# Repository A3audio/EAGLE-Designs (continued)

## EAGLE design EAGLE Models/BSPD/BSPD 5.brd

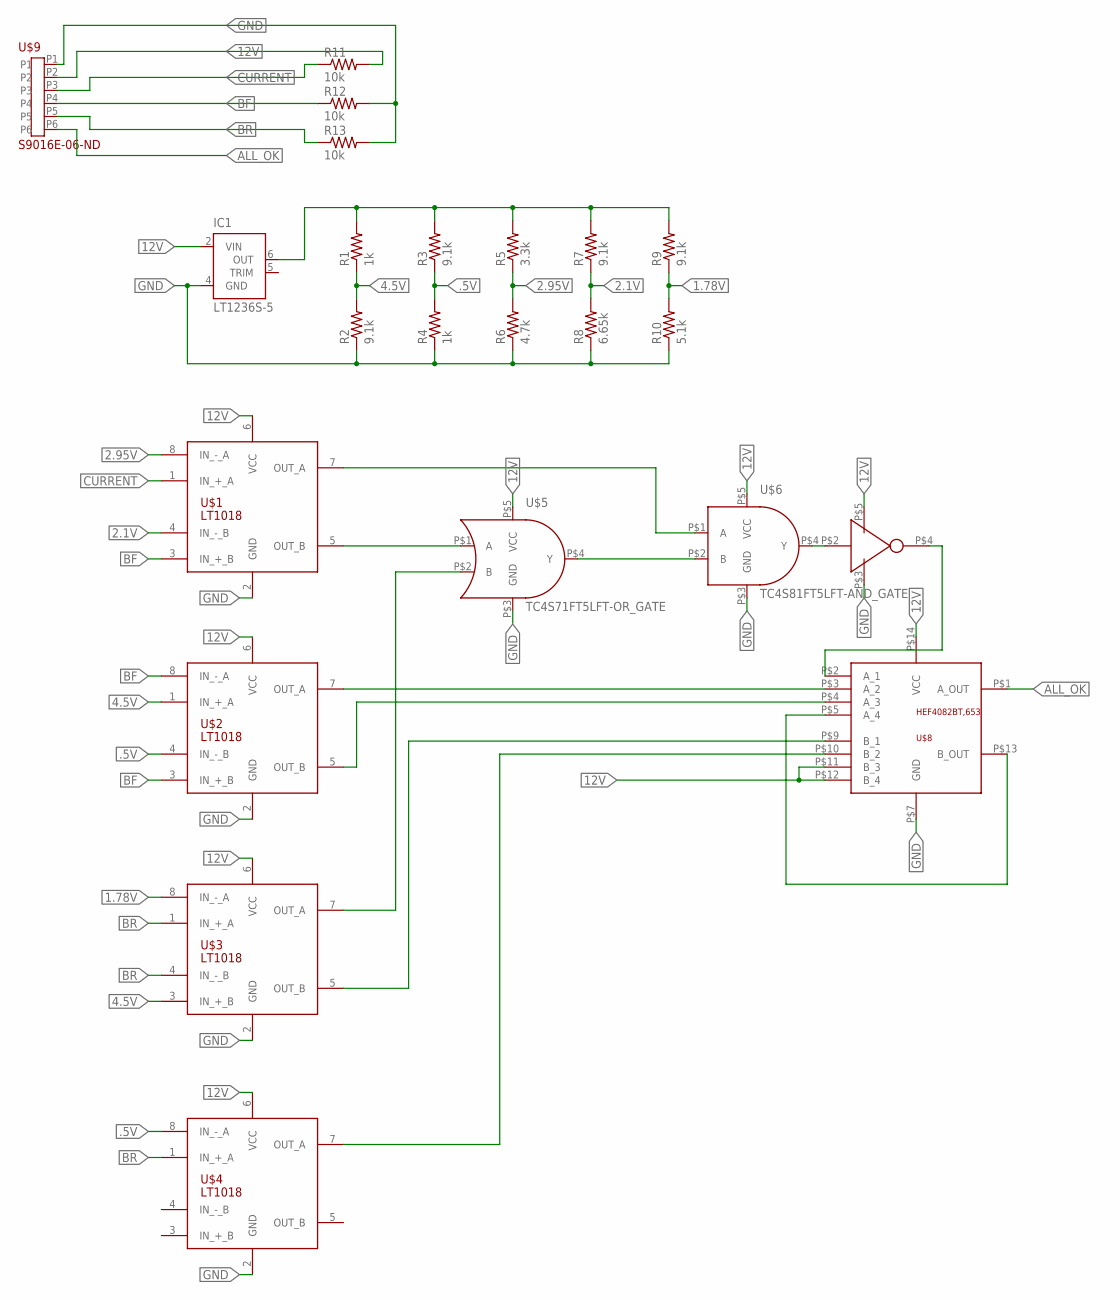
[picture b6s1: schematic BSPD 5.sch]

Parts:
IC1: LT1236S-5; SOIC8
R1, R4: 1k; 0603-RES
R2, R3, R7, R9: 9.1k; 0603-RES
R5: 3.3k; 0603-RES
R6: 4.7k; 0603-RES
R8: 6.65k; 0603-RES
R10: 5.1k; 0603-RES
R11, R12, R13: 10k; 0603-RES
U$1, U$2, U$3, U$4: LT1018; SOIC8
U$5: TC4S71FT5LFT-OR_GATE; SSOP5-P-0.95
U$6: TC4S81FT5LFT-AND_GATE; SSOP5-P-0.95
U$7: TC4S69F(TE85L,F); SSOP5-P-0.95
U$8: HEF4082BT,653; NXP_14_SOIC
U$9: S9016E-06-ND; S9016E-05-ND

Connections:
1.78V: R9.1, R10.2, U$3.8 (IN_-_A)
2.1V: R7.1, R8.2, U$1.4 (IN_-_B)
2.95V: R5.1, R6.2, U$1.8 (IN_-_A)
4.5V: R1.1, R2.2, U$2.1 (IN_+_A), U$3.3 (IN_+_B)
12V: IC1.2 (VIN), R11.2, U$1.6 (VCC), U$2.6 (VCC), U$3.6 (VCC), U$4.6 (VCC), U$5.P$5 (VCC), U$6.P$5 (VCC), U$7.P$5 (VCC), U$8.P$11 (B_3), U$8.P$12 (B_4), U$8.P$14 (VCC), U$9.P2
.5V: R3.1, R4.2, U$2.4 (IN_-_B), U$4.8 (IN_-_A)
ALL_OK: U$8.P$1 (A_OUT), U$9.P6
BF: R12.1, U$1.3 (IN_+_B), U$2.3 (IN_+_B), U$2.8 (IN_-_A), U$9.P4
BR: R13.1, U$3.1 (IN_+_A), U$3.4 (IN_-_B), U$4.1 (IN_+_A), U$9.P5
CURRENT: R11.1, U$1.1 (IN_+_A), U$9.P3
GND: IC1.4 (GND), R2.1, R4.1, R6.1, R8.1, R10.1, R12.2, R13.2, U$1.2 (GND), U$2.2 (GND), U$3.2 (GND), U$4.2 (GND), U$5.P$3 (GND), U$6.P$3 (GND), U$7.P$3 (GND), U$8.P$7 (GND), U$9.P1
unnamed: IC1.6 (OUT), R1.2, R3.2, R5.2, R7.2, R9.2
unnamed: U$1.5 (OUT_B), U$5.P$1 (A)
unnamed: U$3.7 (OUT_A), U$5.P$2 (B)
unnamed: U$5.P$4 (Y), U$6.P$2 (B)
unnamed: U$1.7 (OUT_A), U$6.P$1 (A)
unnamed: U$6.P$4 (Y), U$7.P$2 (IN)
unnamed: U$7.P$4 (OUT), U$8.P$2 (A_1)
unnamed: U$2.7 (OUT_A), U$8.P$3 (A_2)
unnamed: U$2.5 (OUT_B), U$8.P$4 (A_3)
unnamed: U$8.P$5 (A_4), U$8.P$13 (B_OUT)
unnamed: U$3.5 (OUT_B), U$8.P$9 (B_1)
unnamed: U$4.7 (OUT_A), U$8.P$10 (B_2)

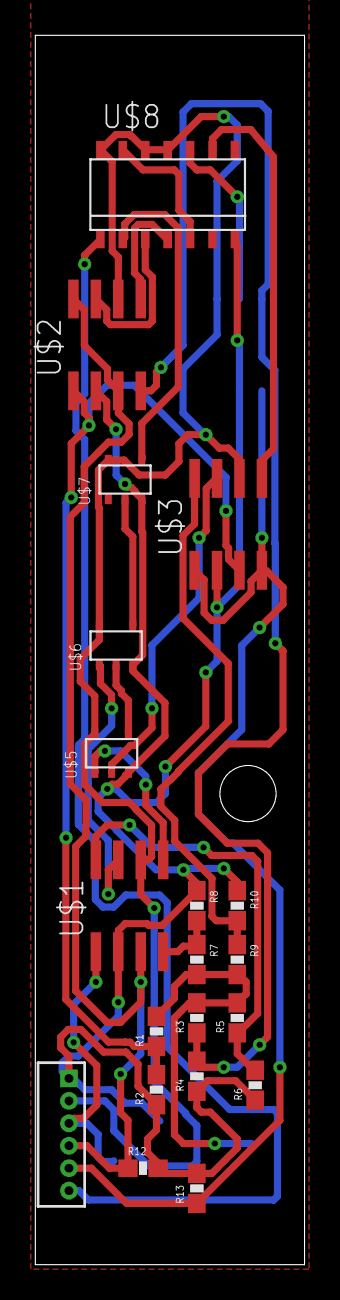
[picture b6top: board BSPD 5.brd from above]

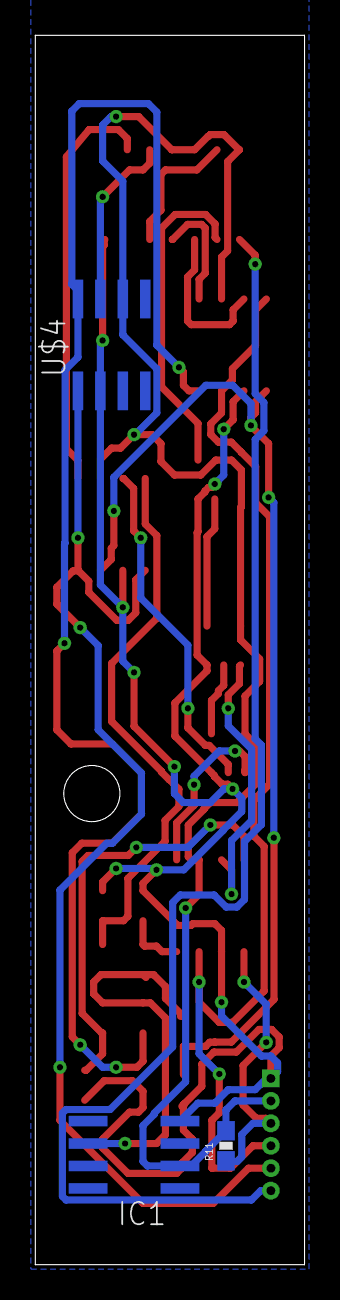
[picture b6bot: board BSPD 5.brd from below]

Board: 2 copper layers, 15.2 x 69.6 mm, 23 parts (3 on the bottom side), 23 nets.

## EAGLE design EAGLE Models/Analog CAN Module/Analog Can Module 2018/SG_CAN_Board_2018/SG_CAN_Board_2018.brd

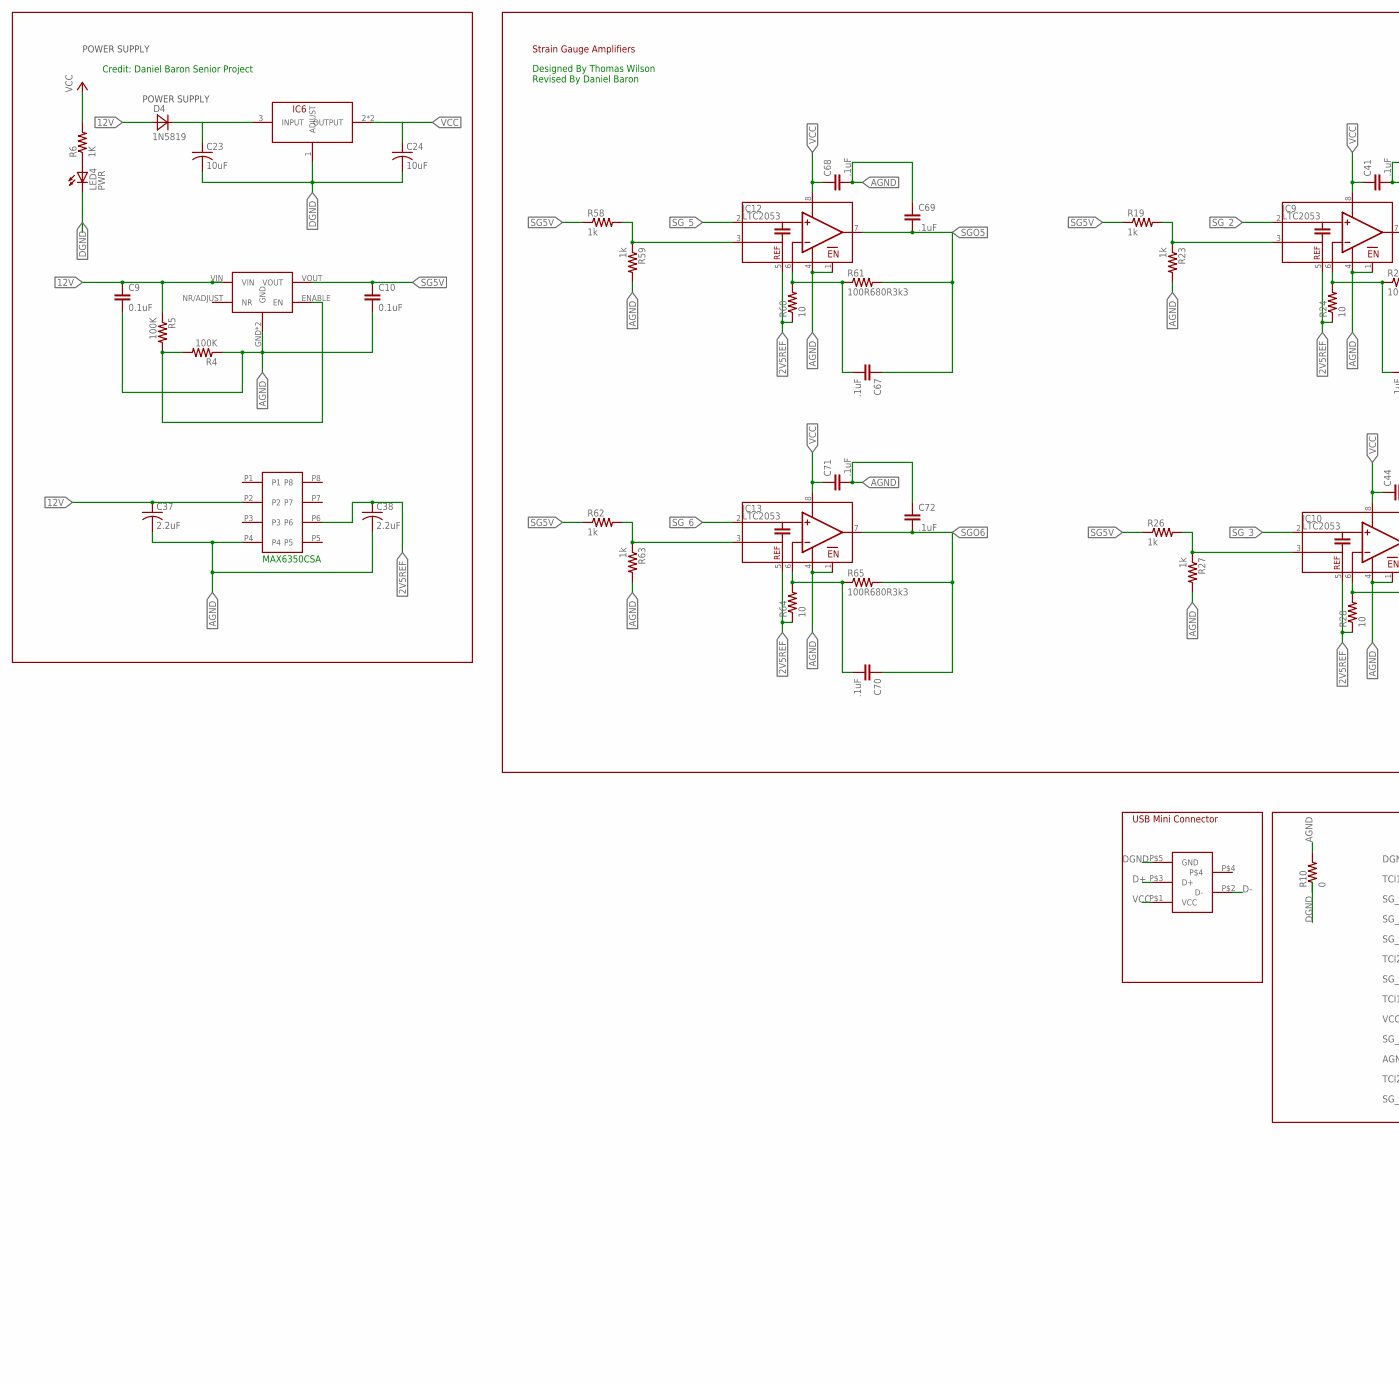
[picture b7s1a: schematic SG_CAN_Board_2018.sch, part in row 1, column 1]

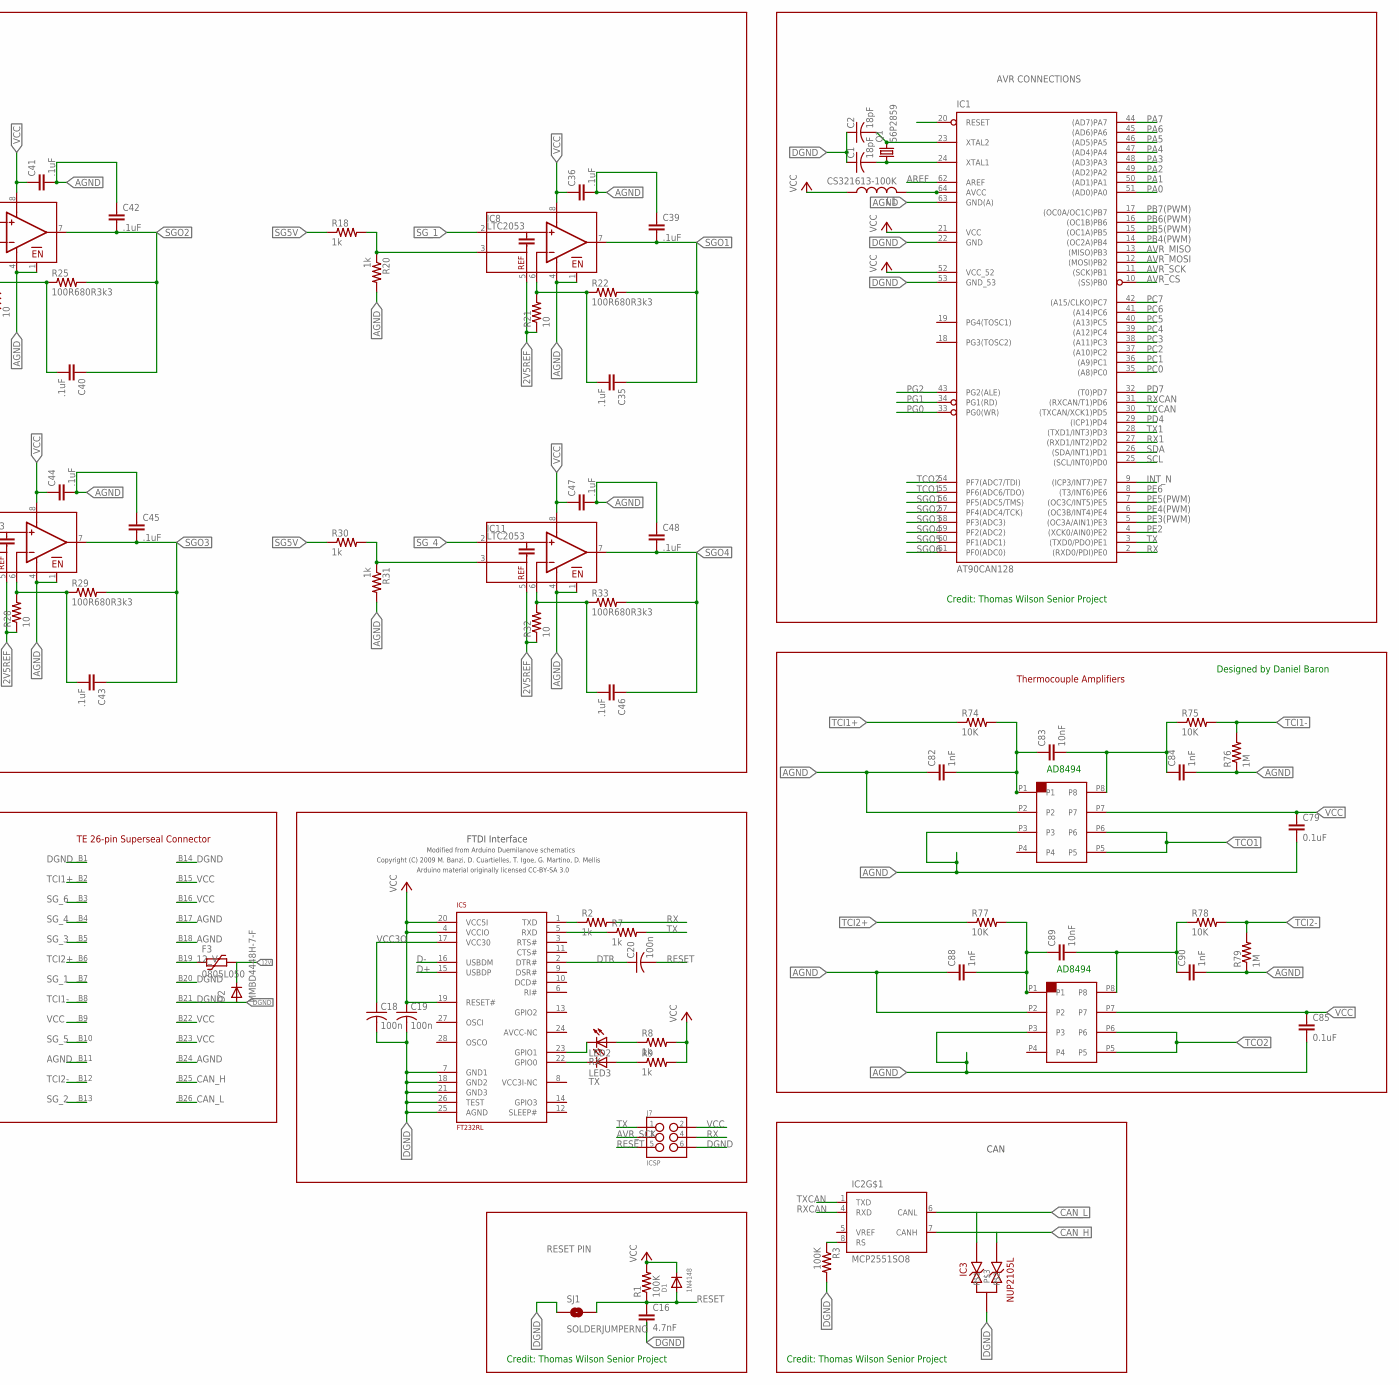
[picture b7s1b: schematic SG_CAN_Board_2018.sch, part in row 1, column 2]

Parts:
C1, C2: 18pF; C0805
C9, C10, C79, C85: 0.1uF; C0603
C16: 4.7nF; 0603-CAP
C18, C19, C20: 100n; C0805
C23, C24: 10uF; C0603
C35, C36, C39, C40, C41, C42, C43, C44, C45, C46, C47, C48, C67, C68, C69, C70, C71, C72: .1uF; 0603-CAP
C37, C38: 2.2uF; C0603
C82, C84, C88, C90: 1nF; C0603
C83, C89: 10nF; C0603
D1: 1N4148; SOD-123
D2: MMBD4448H-7-F; SOT23-3
D4: 1N5819; 1N5819SM
F3: 0805L050; 0805L
IC1: AT90CAN128; TQFP64
IC2: MCP2551SO8; SO08
IC3: NUP2105L; SOT-23
IC4: MAX6350CSA; 8-SOIC
IC5: FT232RL; SSOP28
IC6: NCP1117; SOT-223-4
IC7: REG-104GA-5; REG104GA-5
IC8, IC9, IC10, IC11, IC12, IC13: LTC2053; MSOP8
IC15, IC16: AD8495; 8MSOP
J1: 1734753-1_MINIUSB_CON
J2: SUPERSEAL1.0_26POS
J7: ICSP; 2X3_SMD_FCI_54202-G30
L1: CS321613-100K; L3216C
LED2: RX; CHIPLED_0805
LED3: TX; CHIPLED_0805
LED4: PWR; CHIPLED_0805
Q1: 56P2859; HC49UP
R1, R3: 100K; R0805
R2, R7, R8, R9: 1k; R0805
R4, R5: 100K; M0805
R6: 1K; R0805
R10: 0; 0603-RES
R18, R19, R20, R23, R26, R27, R30, R31, R58, R59, R62, R63: 1k; 0603-RES
R21, R24, R28, R32, R60, R64: 10; 0603-RES
R22, R25, R29, R33, R61, R65: 100R680R3k3; 0603-RES
R74, R75, R77, R78: 10K; 0603-RES
R76, R79: 1M; 0603-RES
SJ1: SOLDERJUMPERNO; SJ_2S-NO

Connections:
2V5REF: C38.1, IC4.P6, IC8.5 (REF), IC9.5 (REF), IC10.5 (REF), IC11.5 (REF), IC12.5 (REF), IC13.5 (REF), R21.1, R24.1, R28.1, R32.1, R60.1, R64.1
5V_REG_IN: C23.1, D4.P$2 (C), IC6.3 (INPUT)
12V: C9.1, C37.1, D2.3 (C), D4.P$1 (A), F3.1, IC4.P2, IC7.VIN, R5.1
12_V: F3.2, J2.B19
AGND: C9.2, C10.2, C36.2, C37.2, C38.2, C39.1, C41.2, C42.1, C44.2, C45.1, C47.2, C48.1, C68.2, C69.1, C71.2, C72.1, C79.2, C82.1, C84.2, C85.2, C88.1, C90.2, IC1.63 (GND(A)), IC4.P4, IC7.GND, IC7.HEATGND (GND), IC8.1 (EN), IC8.4 (V-), IC9.1 (EN), IC9.4 (V-), IC10.1 (EN), IC10.4 (V-), IC11.1 (EN), IC11.4 (V-), IC12.1 (EN), IC12.4 (V-), IC13.1 (EN), IC13.4 (V-), IC15.P2, IC15.P3, IC16.P2, IC16.P3, J2.B11, J2.B17, J2.B18, J2.B24, R4.1, R10.2, R20.2, R23.2, R27.2, R31.2, R59.2, R63.2, R76.1, R79.1
AREF: IC1.62 (AREF)
AVR_CS: IC1.10 ((SS)PB0)
AVR_MISO: IC1.13 ((MISO)PB3)
AVR_MOSI: IC1.12 ((MOSI)PB2)
AVR_SCK: IC1.11 ((SCK)PB1), J7.3
CAN_H: IC2.7 (CANH), IC3.2, J2.B25
CAN_L: IC2.6 (CANL), IC3.1, J2.B26
D+: IC5.15 (USBDP), J1.P$3 (D+)
D-: IC5.16 (USBDM), J1.P$2 (D-)
DGND: C1.1, C2.1, C18.2, C19.2, C23.2, C24.2, D2.1 (A), IC1.22 (GND), IC1.53 (GND_53), IC2.2 (GND), IC3.3, IC5.7 (GND1), IC5.18 (GND2), IC5.21 (GND3), IC5.25 (AGND), IC5.26 (TEST), IC6.1 (ADJUST), J1.P$5 (GND), J2.B1, J2.B14, J2.B20, J2.B21, J7.6, LED4.C, R3.2, R10.1, SJ1.1
DTR: C20.1, IC5.2 (DTR#)
INT_N: IC1.9 ((ICP3/INT7)PE7)
M8RXD: IC5.1 (TXD), R2.1
M8TXD: IC5.5 (RXD), R7.1
unnamed: C35.2, IC8.6 (RG), R21.2, R22.1
unnamed: IC7.ENABLE (EN), R4.2, R5.2
unnamed: IC8.3 (+IN), R18.2, R20.1
unnamed: IC9.3 (+IN), R19.2, R23.1
unnamed: IC2.8 (RS), R3.1
unnamed: C40.2, IC9.6 (RG), R24.2, R25.1
unnamed: IC10.3 (+IN), R26.2, R27.1
unnamed: LED4.A, R6.1
unnamed: C43.2, IC10.6 (RG), R28.2, R29.1
unnamed: C1.2, IC1.24 (XTAL1), Q1.1
unnamed: IC11.3 (+IN), R30.2, R31.1
unnamed: C46.2, IC11.6 (RG), R32.2, R33.1
unnamed: IC1.64 (AVCC), L1.2
unnamed: IC12.3 (+IN), R58.2, R59.1
unnamed: C67.2, IC12.6 (RG), R60.2, R61.1
unnamed: IC13.3 (+IN), R62.2, R63.1
unnamed: C70.2, IC13.6 (RG), R64.2, R65.1
unnamed: IC5.23 (GPIO1), LED2.C
unnamed: IC5.22 (GPIO0), LED3.C
unnamed: LED2.A, R8.1
unnamed: LED3.A, R9.1
unnamed: C88.2, C89.1, IC16.P1, R77.2
unnamed: C83.2, C84.1, IC15.P8, R75.1
unnamed: C89.2, C90.1, IC16.P8, R78.1
unnamed: C82.2, C83.1, IC15.P1, R74.2
PA0: IC1.51 ((AD0)PA0)
PA1: IC1.50 ((AD1)PA1)
PA2: IC1.49 ((AD2)PA2)
PA3: IC1.48 ((AD3)PA3)
PA4: IC1.47 ((AD4)PA4)
PA5: IC1.46 ((AD5)PA5)
PA6: IC1.45 ((AD6)PA6)
PA7: IC1.44 ((AD7)PA7)
PB4(PWM): IC1.14 ((OC2A)PB4)
PB5(PWM): IC1.15 ((OC1A)PB5)
PB6(PWM): IC1.16 ((OC1B)PB6)
PB7(PWM): IC1.17 ((OC0A/OC1C)PB7)
PC0: IC1.35 ((A8)PC0)
PC1: IC1.36 ((A9)PC1)
PC2: IC1.37 ((A10)PC2)
PC3: IC1.38 ((A11)PC3)
PC4: IC1.39 ((A12)PC4)
PC5: IC1.40 ((A13)PC5)
PC6: IC1.41 ((A14)PC6)
PC7: IC1.42 ((A15/CLKO)PC7)
PD4: IC1.29 ((ICP1)PD4)
PD7: IC1.32 ((T0)PD7)
PE2: IC1.4 ((XCK0/AIN0)PE2)
PE3(PWM): IC1.5 ((OC3A/AIN1)PE3)
PE4(PWM): IC1.6 ((OC3B/INT4)PE4)
PE5(PWM): IC1.7 ((OC3C/INT5)PE5)
PE6: IC1.8 ((T3/INT6)PE6)
PG0: IC1.33 (PG0(WR))
PG1: IC1.34 (PG1(RD))
PG2: IC1.43 (PG2(ALE))
RESET: C16.1, C20.2, D1.A, IC1.20 (RESET), J7.5, R1.1, SJ1.2
RX: IC1.2 ((RXD0/PDI)PE0), J7.4, R2.2
RX1: IC1.27 ((RXD1/INT2)PD2)
RXCAN: IC1.31 ((RXCAN/T1)PD6), IC2.4 (RXD)
SCL: IC1.25 ((SCL/INT0)PD0)
SDA: IC1.26 ((SDA/INT1)PD1)
SG5V: C10.1, IC7.VOUT, R18.1, R19.1, R26.1, R30.1, R58.1, R62.1
SGO1: C35.1, C39.2, IC1.56 (PF5(ADC5/TMS)), IC8.7 (OUT), R22.2
SGO2: C40.1, C42.2, IC1.57 (PF4(ADC4/TCK)), IC9.7 (OUT), R25.2
SGO3: C43.1, C45.2, IC1.58 (PF3(ADC3)), IC10.7 (OUT), R29.2
SGO4: C46.1, C48.2, IC1.59 (PF2(ADC2)), IC11.7 (OUT), R33.2
SGO5: C67.1, C69.2, IC1.60 (PF1(ADC1)), IC12.7 (OUT), R61.2
SGO6: C70.1, C72.2, IC1.61 (PF0(ADC0)), IC13.7 (OUT), R65.2
SG_1: IC8.2 (-IN), J2.B7
SG_2: IC9.2 (-IN), J2.B13
SG_3: IC10.2 (-IN), J2.B5
SG_4: IC11.2 (-IN), J2.B4
SG_5: IC12.2 (-IN), J2.B10
SG_6: IC13.2 (-IN), J2.B3
TCI1+: J2.B2, R74.1
TCI1-: J2.B8, R75.2, R76.2
TCI2+: J2.B6, R77.1
TCI2-: J2.B12, R78.2, R79.2
TCO1: IC1.55 (PF6(ADC6/TDO)), IC15.P5, IC15.P6
TCO2: IC1.54 (PF7(ADC7/TDI)), IC16.P5, IC16.P6
TX: IC1.3 ((TXD0/PDO)PE1), J7.1, R7.2
TX1: IC1.28 ((TXD1/INT3)PD3)
TXCAN: IC1.30 ((TXCAN/XCK1)PD5), IC2.1 (TXD)
VCC: C19.1, C24.1, C36.1, C41.1, C44.1, C47.1, C68.1, C71.1, C79.1, C85.1, D1.C, IC1.21 (VCC), IC1.52 (VCC_52), IC2.3 (VCC), IC5.4 (VCCIO), IC5.19 (RESET#), IC5.20 (VCC5I), IC6.2 (OUTPUT), IC6.4 (OUTPUT), IC8.8 (V+), IC9.8 (V+), IC10.8 (V+), IC11.8 (V+), IC12.8 (V+), IC13.8 (V+), IC15.P7, IC16.P7, J1.P$1 (VCC), J2.B9, J2.B15, J2.B16, J2.B22, J2.B23, J7.2, L1.1, R1.2, R6.2, R8.2, R9.2
VCC3O: C18.1, IC5.17 (VCC30)
XTAL1: C2.2, IC1.23 (XTAL2), Q1.2

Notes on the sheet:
CAN
AVR CONNECTIONS
Thermocouple Amplifiers
Credit: Thomas Wilson Senior Project
Designed by Daniel Baron
AD8494
Strain Gauge Amplifiers
RESET PIN
FTDI Interface
Modified from Arduino Duemilanove schematics
Copyright (C) 2009 M. Banzi, D. Cuartielles, T. Igoe, G. Martino, D. Mellis
Arduino material originally licensed CC-BY-SA 3.0
Designed By Thomas Wilson Revised By Daniel Baron
USB Mini Connector
POWER SUPPLY
MAX6350CSA
Credit: Daniel Baron Senior Project
TE 26-pin Superseal Connector

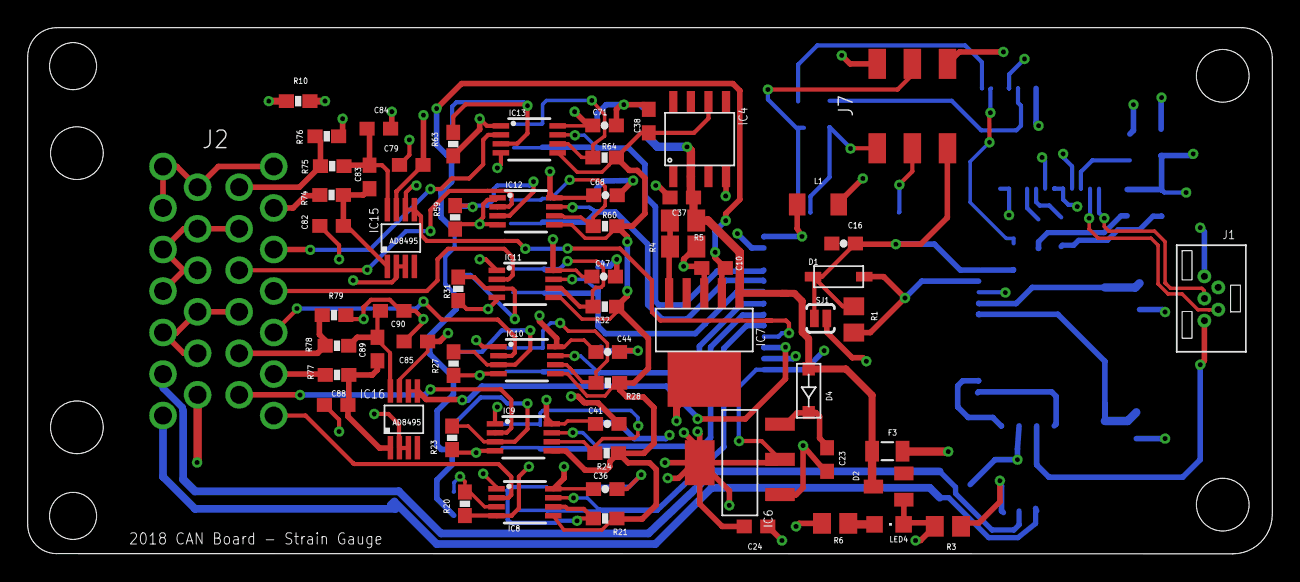
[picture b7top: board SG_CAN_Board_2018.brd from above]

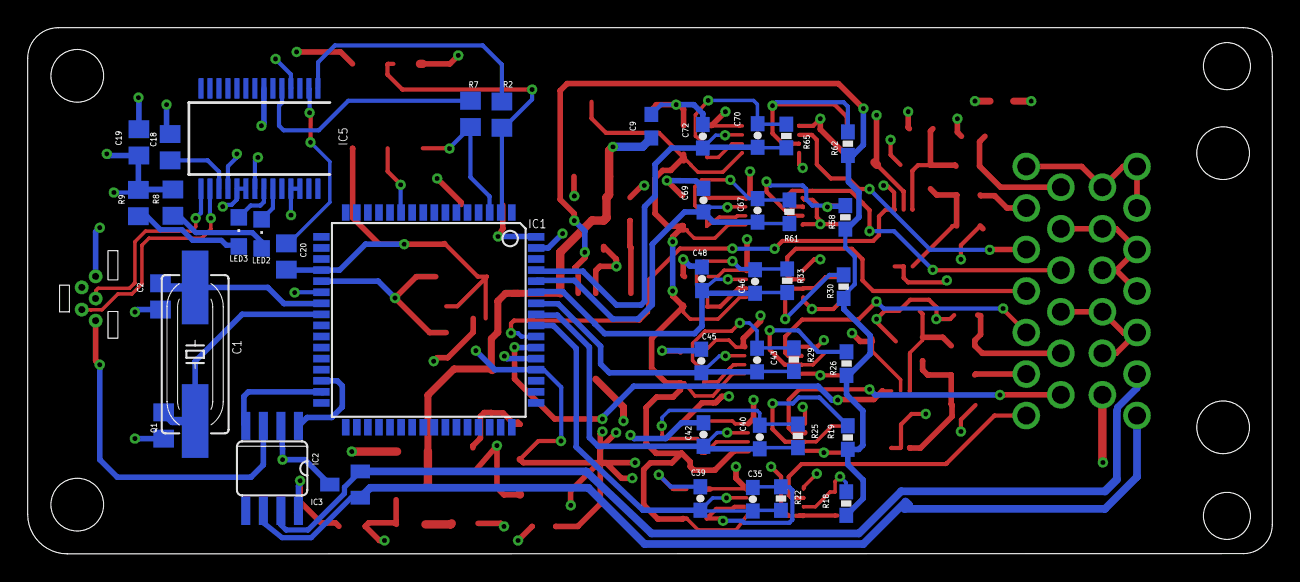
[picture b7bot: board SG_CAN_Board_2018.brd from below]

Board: 4 copper layers, 89.9 x 38.0 mm, 106 parts (41 on the bottom side), 66 nets.

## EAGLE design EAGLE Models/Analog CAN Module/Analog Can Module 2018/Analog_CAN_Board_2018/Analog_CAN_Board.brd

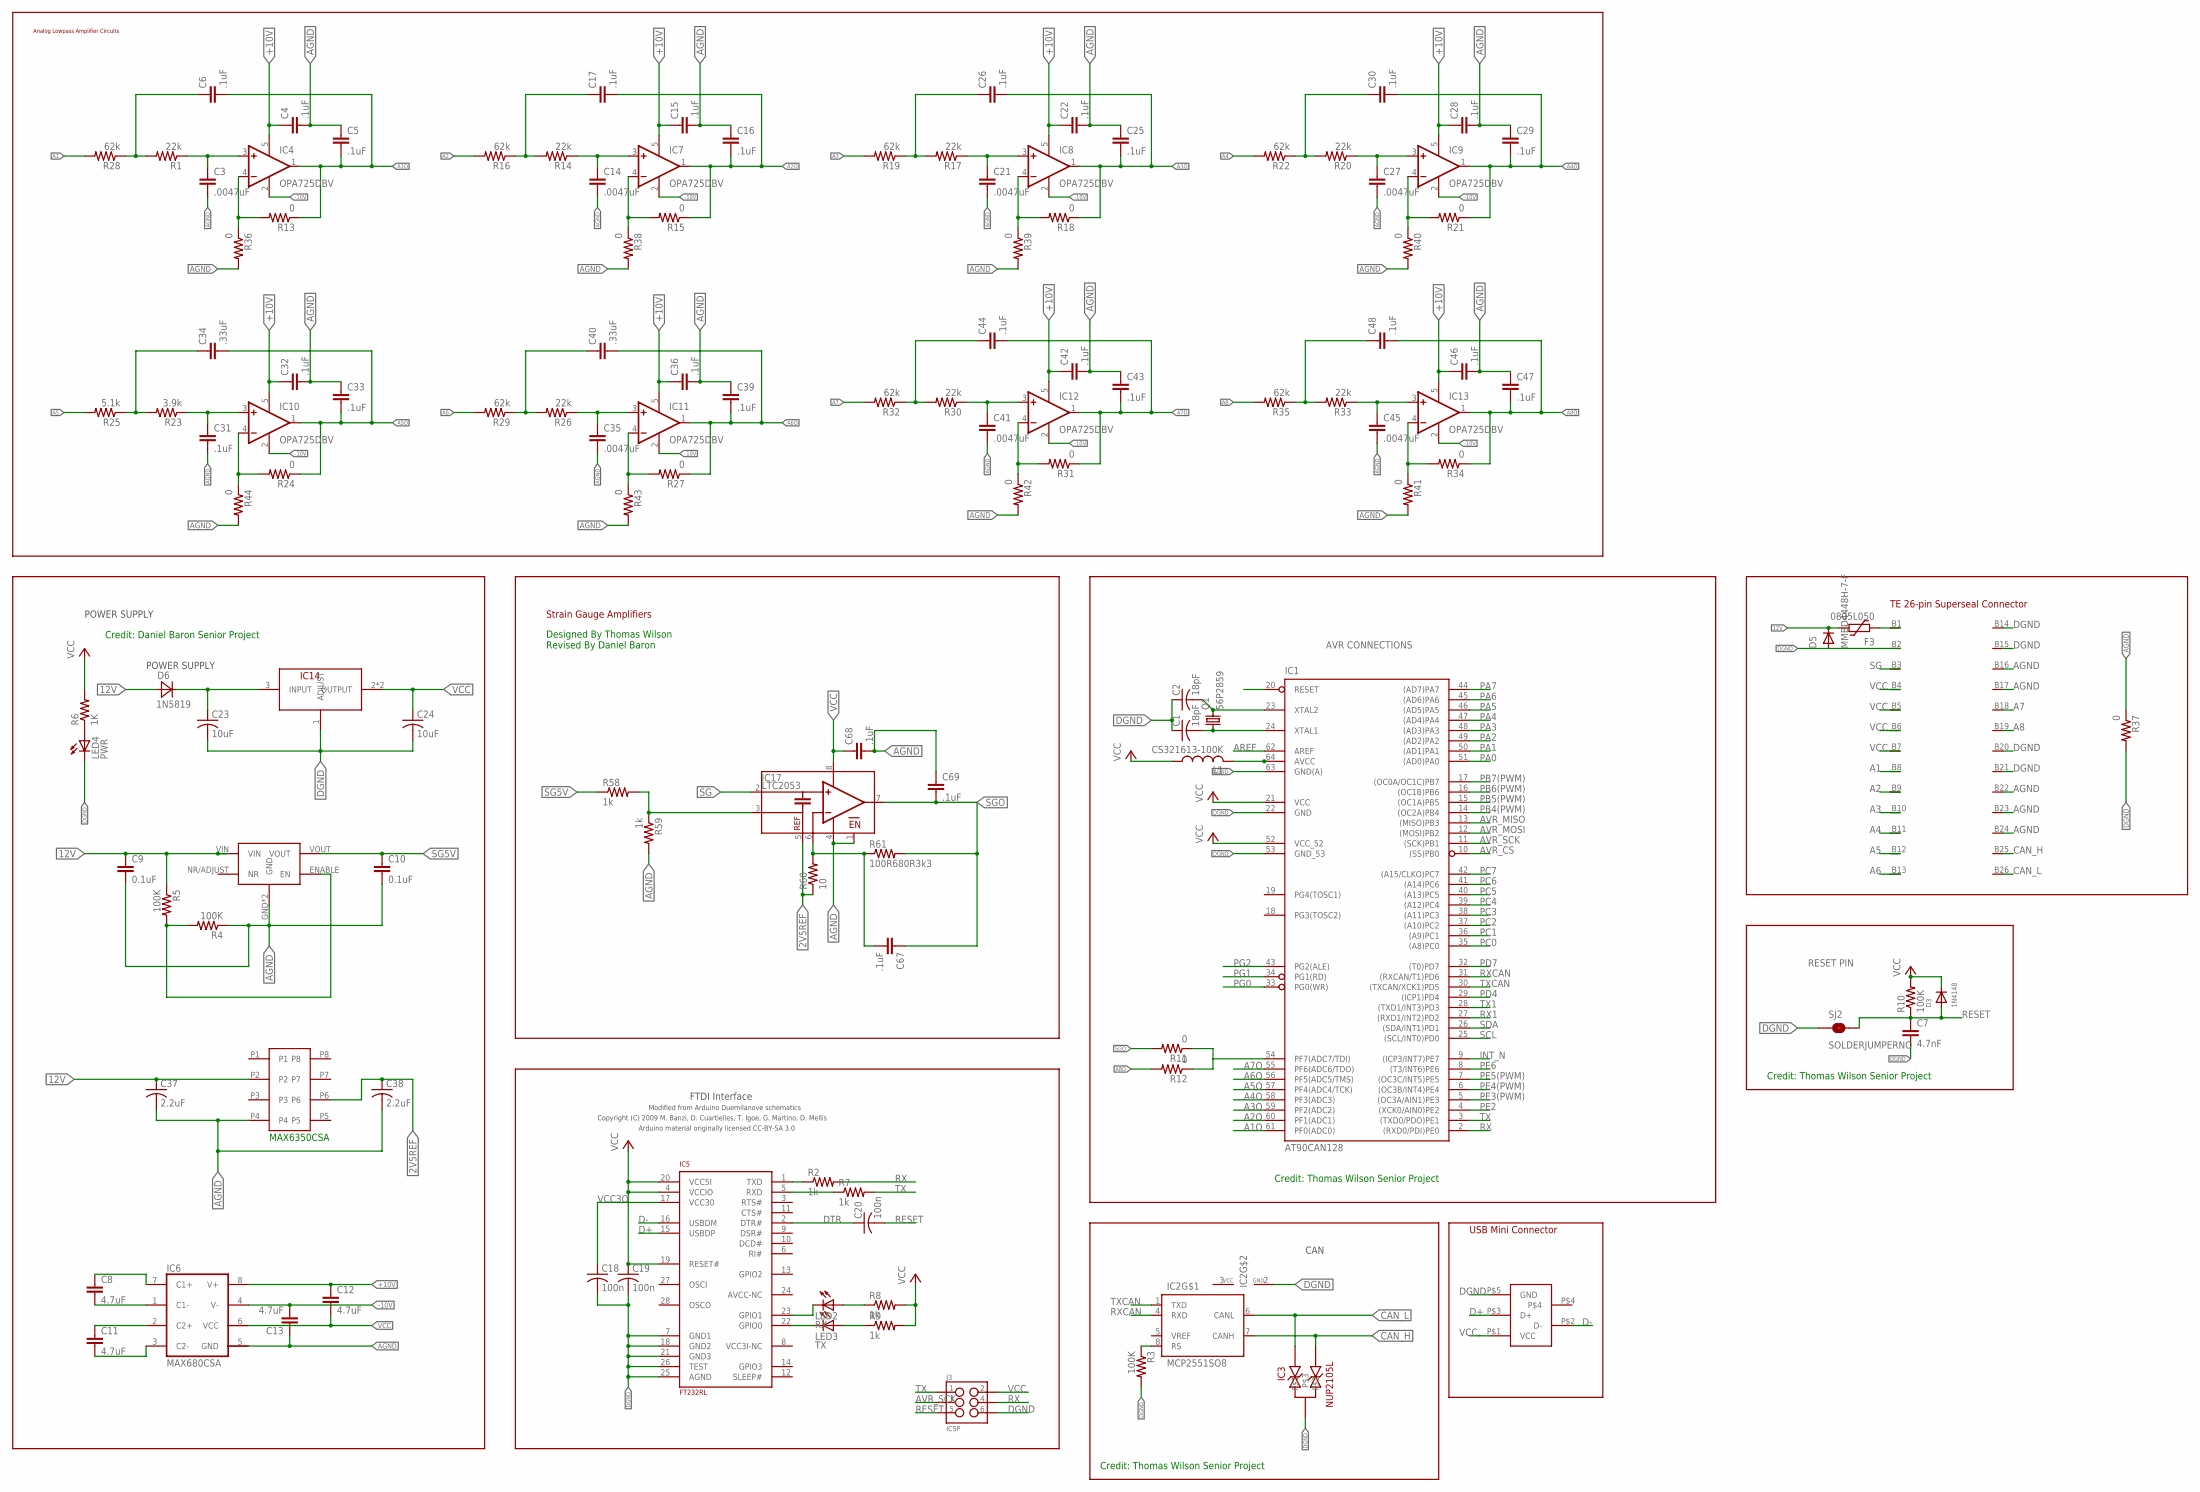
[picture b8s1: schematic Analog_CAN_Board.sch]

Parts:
C1, C2: 18pF; C0805
C3, C14, C21, C27, C35, C41, C45: .0047uF; 0603-CAP
C4, C5, C6, C15, C16, C17, C22, C25, C26, C28, C29, C30, C31, C32, C33, C36, C39, C42, C43, C44, C46, C47, C48, C67, C68, C69: .1uF; 0603-CAP
C7: 4.7nF; 0603-CAP
C8, C11, C12, C13: 4.7uF; 0603-CAP
C9, C10: 0.1uF; C0603
C18, C19, C20: 100n; C0805
C23, C24: 10uF; C0603
C34, C40: .33uF; 0603-CAP
C37, C38: 2.2uF; C0603
D3: 1N4148; SOD-123
D5: MMBD4448H-7-F; SOT23-3
D6: 1N5819; 1N5819SM
F3: 0805L050; 0805L
IC1: AT90CAN128; TQFP64
IC2: MCP2551SO8; SO08
IC3: NUP2105L; SOT-23
IC4, IC7, IC8, IC9, IC10, IC11, IC12, IC13: OPA725DBV; SOT23-5
IC5: FT232RL; SSOP28
IC6: MAX680CSA; SO08
IC14: NCP1117; SOT-223-4
IC15: IC15; REG104GA-5
IC16: MAX6350CSA; 8-SOIC
IC17: LTC2053; MSOP8
J1: 1734753-1_MINIUSB_CON
J2: SUPERSEAL1.0_26POS
J3: ICSP; 2X3_SMD_FCI_54202-G30
L1: CS321613-100K; L3216C
LED2: RX; CHIPLED_0805
LED3: TX; CHIPLED_0805
LED4: PWR; CHIPLED_0805
Q1: 56P2859; HC49UP
R1, R14, R17, R20, R26, R30, R33: 22k; 0603-RES
R2, R7, R8, R9: 1k; R0805
R3, R10: 100K; R0805
R4, R5: 100K; M0805
R6: 1K; R0805
R11, R12, R13, R15, R18, R21, R24, R27, R31, R34, R36, R37, R38, R39, R40, R41, R42, R43, R44: 0; 0603-RES
R16, R19, R22, R28, R29, R32, R35: 62k; 0603-RES
R23: 3.9k; 0603-RES
R25: 5.1k; 0603-RES
R58, R59: 1k; 0603-RES
R60: 10; 0603-RES
R61: 100R680R3k3; 0603-RES
SJ2: SOLDERJUMPERNO; SJ_2S-NO

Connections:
2V5REF: C38.1, IC16.P6, IC17.5 (REF), R60.1
5V_REG_IN: C23.1, D6.P$2 (C), IC14.3 (INPUT)
12V: C9.1, C37.1, D5.3 (C), D6.P$1 (A), F3.1, IC15.VIN, IC16.P2, R5.1
+10V: C4.1, C12.1, C15.1, C22.1, C28.1, C32.1, C36.1, C42.1, C46.1, IC4.5 (V+), IC6.8 (V+), IC7.5 (V+), IC8.5 (V+), IC9.5 (V+), IC10.5 (V+), IC11.5 (V+), IC12.5 (V+), IC13.5 (V+)
-10V: C13.2, IC4.2 (V-), IC6.4 (V-), IC7.2 (V-), IC8.2 (V-), IC9.2 (V-), IC10.2 (V-), IC11.2 (V-), IC12.2 (V-), IC13.2 (V-)
A1: J2.B8, R28.2
A1O: C5.2, C6.2, IC1.61 (PF0(ADC0)), IC4.1 (OUT), R13.1
A2: J2.B9, R16.2
A2O: C16.2, C17.2, IC1.60 (PF1(ADC1)), IC7.1 (OUT), R15.1
A3: J2.B10, R19.2
A3O: C25.2, C26.2, IC1.59 (PF2(ADC2)), IC8.1 (OUT), R18.1
A4: J2.B11, R22.2
A4O: C29.2, C30.2, IC1.58 (PF3(ADC3)), IC9.1 (OUT), R21.1
A5: J2.B12, R25.2
A5O: C33.2, C34.2, IC1.57 (PF4(ADC4/TCK)), IC10.1 (OUT), R24.1
A6: J2.B13, R29.2
A6O: C39.2, C40.2, IC1.56 (PF5(ADC5/TMS)), IC11.1 (OUT), R27.1
A7: J2.B18, R32.2
A7O: C43.2, C44.2, IC1.55 (PF6(ADC6/TDO)), IC12.1 (OUT), R31.1
A8: J2.B19, R35.2
A8O: C47.2, C48.2, IC13.1 (OUT), R12.2, R34.1
AGND: C3.2, C4.2, C5.1, C9.2, C10.2, C13.1, C14.2, C15.2, C16.1, C21.2, C22.2, C25.1, C27.2, C28.2, C29.1, C31.2, C32.2, C33.1, C35.2, C36.2, C37.2, C38.2, C39.1, C41.2, C42.2, C43.1, C45.2, C46.2, C47.1, C68.2, C69.1, IC1.63 (GND(A)), IC6.5 (GND), IC15.GND, IC15.HEATGND (GND), IC16.P4, IC17.1 (EN), IC17.4 (V-), J2.B16, J2.B17, J2.B22, J2.B23, J2.B24, R4.1, R36.2, R37.1, R38.2, R39.2, R40.2, R41.2, R42.2, R43.2, R44.2, R59.2
AREF: IC1.62 (AREF)
AVR_CS: IC1.10 ((SS)PB0)
AVR_MISO: IC1.13 ((MISO)PB3)
AVR_MOSI: IC1.12 ((MOSI)PB2)
AVR_SCK: IC1.11 ((SCK)PB1), J3.3
CAN_H: IC2.7 (CANH), IC3.2, J2.B25
CAN_L: IC2.6 (CANL), IC3.1, J2.B26
D+: IC5.15 (USBDP), J1.P$3 (D+)
D-: IC5.16 (USBDM), J1.P$2 (D-)
DGND: C1.1, C2.1, C7.2, C18.2, C19.2, C23.2, C24.2, D5.1 (A), IC1.22 (GND), IC1.53 (GND_53), IC2.2 (GND), IC3.3, IC5.7 (GND1), IC5.18 (GND2), IC5.21 (GND3), IC5.25 (AGND), IC5.26 (TEST), IC14.1 (ADJUST), J1.P$5 (GND), J2.B2, J2.B14, J2.B15, J2.B20, J2.B21, J3.6, LED4.C, R3.2, R37.2, SJ2.1
DTR: C20.1, IC5.2 (DTR#)
INT_N: IC1.9 ((ICP3/INT7)PE7)
M8RXD: IC5.1 (TXD), R2.1
M8TXD: IC5.5 (RXD), R7.1
unnamed: F3.2, J2.B1
unnamed: IC15.ENABLE (EN), R4.2, R5.2
unnamed: C6.1, R1.2, R28.1
unnamed: IC2.8 (RS), R3.1
unnamed: LED4.A, R6.1
unnamed: C1.2, IC1.24 (XTAL1), Q1.1
unnamed: C3.1, IC4.3 (+IN), R1.1
unnamed: IC1.54 (PF7(ADC7/TDI)), R11.1, R12.1
unnamed: IC4.4 (-IN), R13.2, R36.1
unnamed: C8.1, IC6.7 (C1+)
unnamed: C11.1, IC6.2 (C2+)
unnamed: IC1.64 (AVCC), L1.2
unnamed: C8.2, IC6.1 (C1-)
unnamed: C11.2, IC6.3 (C2-)
unnamed: C14.1, IC7.3 (+IN), R14.1
unnamed: IC7.4 (-IN), R15.2, R38.1
unnamed: C17.1, R14.2, R16.1
unnamed: IC17.3 (+IN), R58.2, R59.1
unnamed: C67.2, IC17.6 (RG), R60.2, R61.1
unnamed: C21.1, IC8.3 (+IN), R17.1
unnamed: IC8.4 (-IN), R18.2, R39.1
unnamed: IC5.23 (GPIO1), LED2.C
unnamed: C26.1, R17.2, R19.1
unnamed: IC5.22 (GPIO0), LED3.C
unnamed: LED2.A, R8.1
unnamed: LED3.A, R9.1
unnamed: C27.1, IC9.3 (+IN), R20.1
unnamed: IC9.4 (-IN), R21.2, R40.1
unnamed: C30.1, R20.2, R22.1
unnamed: C31.1, IC10.3 (+IN), R23.1
unnamed: IC10.4 (-IN), R24.2, R44.1
unnamed: C34.1, R23.2, R25.1
unnamed: C35.1, IC11.3 (+IN), R26.1
unnamed: IC11.4 (-IN), R27.2, R43.1
unnamed: C40.1, R26.2, R29.1
unnamed: C41.1, IC12.3 (+IN), R30.1
unnamed: IC12.4 (-IN), R31.2, R42.1
unnamed: C44.1, R30.2, R32.1
unnamed: C45.1, IC13.3 (+IN), R33.1
unnamed: IC13.4 (-IN), R34.2, R41.1
unnamed: C48.1, R33.2, R35.1
PA0: IC1.51 ((AD0)PA0)
PA1: IC1.50 ((AD1)PA1)
PA2: IC1.49 ((AD2)PA2)
PA3: IC1.48 ((AD3)PA3)
PA4: IC1.47 ((AD4)PA4)
PA5: IC1.46 ((AD5)PA5)
PA6: IC1.45 ((AD6)PA6)
PA7: IC1.44 ((AD7)PA7)
PB4(PWM): IC1.14 ((OC2A)PB4)
PB5(PWM): IC1.15 ((OC1A)PB5)
PB6(PWM): IC1.16 ((OC1B)PB6)
PB7(PWM): IC1.17 ((OC0A/OC1C)PB7)
PC0: IC1.35 ((A8)PC0)
PC1: IC1.36 ((A9)PC1)
PC2: IC1.37 ((A10)PC2)
PC3: IC1.38 ((A11)PC3)
PC4: IC1.39 ((A12)PC4)
PC5: IC1.40 ((A13)PC5)
PC6: IC1.41 ((A14)PC6)
PC7: IC1.42 ((A15/CLKO)PC7)
PD4: IC1.29 ((ICP1)PD4)
PD7: IC1.32 ((T0)PD7)
PE2: IC1.4 ((XCK0/AIN0)PE2)
PE3(PWM): IC1.5 ((OC3A/AIN1)PE3)
PE4(PWM): IC1.6 ((OC3B/INT4)PE4)
PE5(PWM): IC1.7 ((OC3C/INT5)PE5)
PE6: IC1.8 ((T3/INT6)PE6)
PG0: IC1.33 (PG0(WR))
PG1: IC1.34 (PG1(RD))
PG2: IC1.43 (PG2(ALE))
RESET: C7.1, C20.2, D3.A, IC1.20 (RESET), J3.5, R10.1, SJ2.2
RX: IC1.2 ((RXD0/PDI)PE0), J3.4, R2.2
RX1: IC1.27 ((RXD1/INT2)PD2)
RXCAN: IC1.31 ((RXCAN/T1)PD6), IC2.4 (RXD)
SCL: IC1.25 ((SCL/INT0)PD0)
SDA: IC1.26 ((SDA/INT1)PD1)
SG: IC17.2 (-IN), J2.B3
SG5V: C10.1, IC15.VOUT, R58.1
SGO: C67.1, C69.2, IC17.7 (OUT), R11.2, R61.2
TX: IC1.3 ((TXD0/PDO)PE1), J3.1, R7.2
TX1: IC1.28 ((TXD1/INT3)PD3)
TXCAN: IC1.30 ((TXCAN/XCK1)PD5), IC2.1 (TXD)
VCC: C12.2, C19.1, C24.1, C68.1, D3.C, IC1.21 (VCC), IC1.52 (VCC_52), IC2.3 (VCC), IC5.4 (VCCIO), IC5.19 (RESET#), IC5.20 (VCC5I), IC6.6 (VCC), IC14.2 (OUTPUT), IC14.4 (OUTPUT), IC17.8 (V+), J1.P$1 (VCC), J2.B4, J2.B5, J2.B6, J2.B7, J3.2, L1.1, R6.2, R8.2, R9.2, R10.2
VCC3O: C18.1, IC5.17 (VCC30)
XTAL1: C2.2, IC1.23 (XTAL2), Q1.2

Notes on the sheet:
CAN
AVR CONNECTIONS
Credit: Thomas Wilson Senior Project
Strain Gauge Amplifiers
POWER SUPPLY
FTDI Interface
Modified from Arduino Duemilanove schematics
Copyright (C) 2009 M. Banzi, D. Cuartielles, T. Igoe, G. Martino, D. Mellis
Arduino material originally licensed CC-BY-SA 3.0
MAX6350CSA
Designed By Thomas Wilson Revised By Daniel Baron
TE 26-pin Superseal Connector
RESET PIN
USB Mini Connector
Credit: Daniel Baron Senior Project
Analog Lowpass Amplifier Circuits

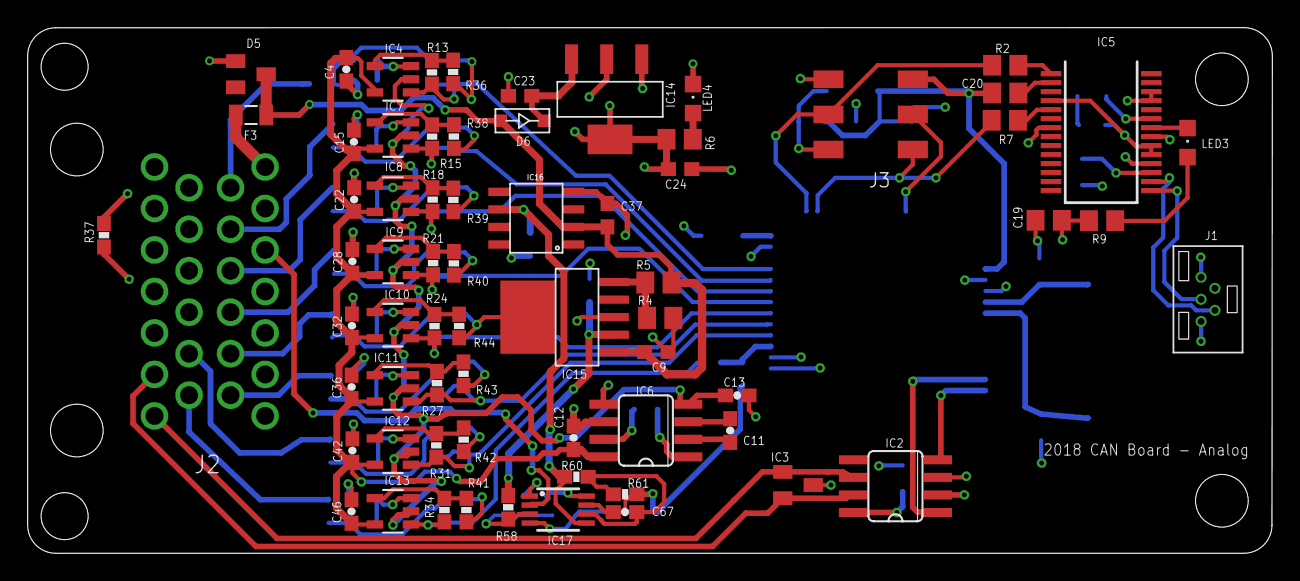
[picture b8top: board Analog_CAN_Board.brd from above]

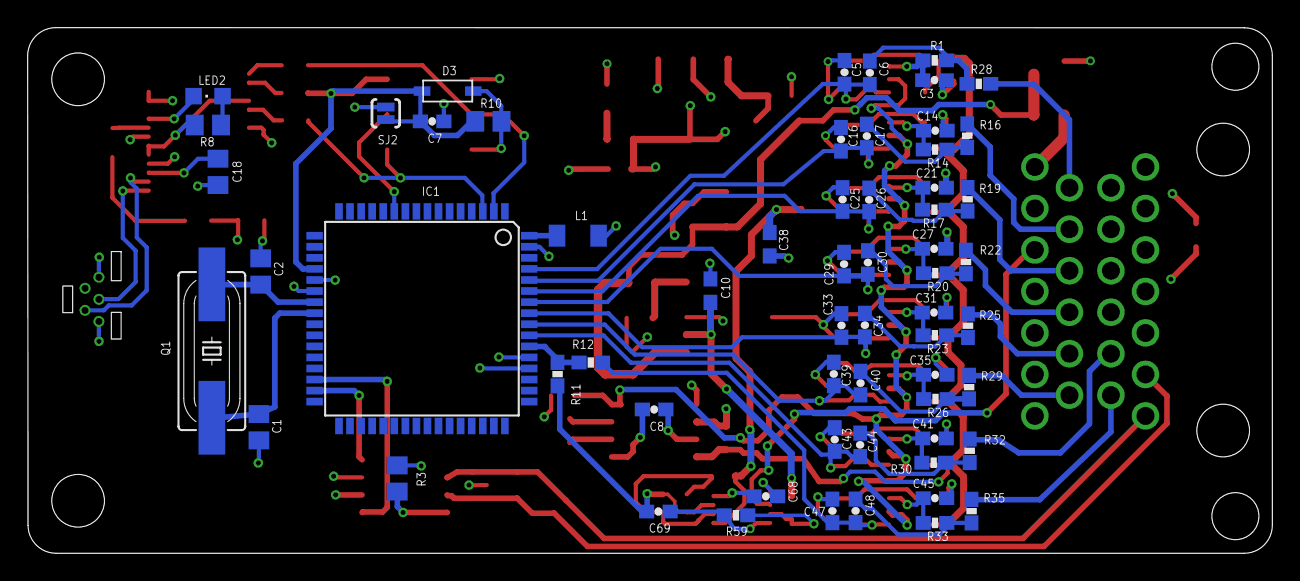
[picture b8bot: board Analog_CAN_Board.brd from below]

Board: 4 copper layers, 90.0 x 38.0 mm, 129 parts (61 on the bottom side), 83 nets.
